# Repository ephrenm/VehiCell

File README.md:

**Goal:** Create a single module which combines vehicle CANbus, GPS and accelerometer data into a single stream to be stored in a cloud database using LTE CAT-M1 cellular technology.

**Current Task:** Routing

Current WIP layout:

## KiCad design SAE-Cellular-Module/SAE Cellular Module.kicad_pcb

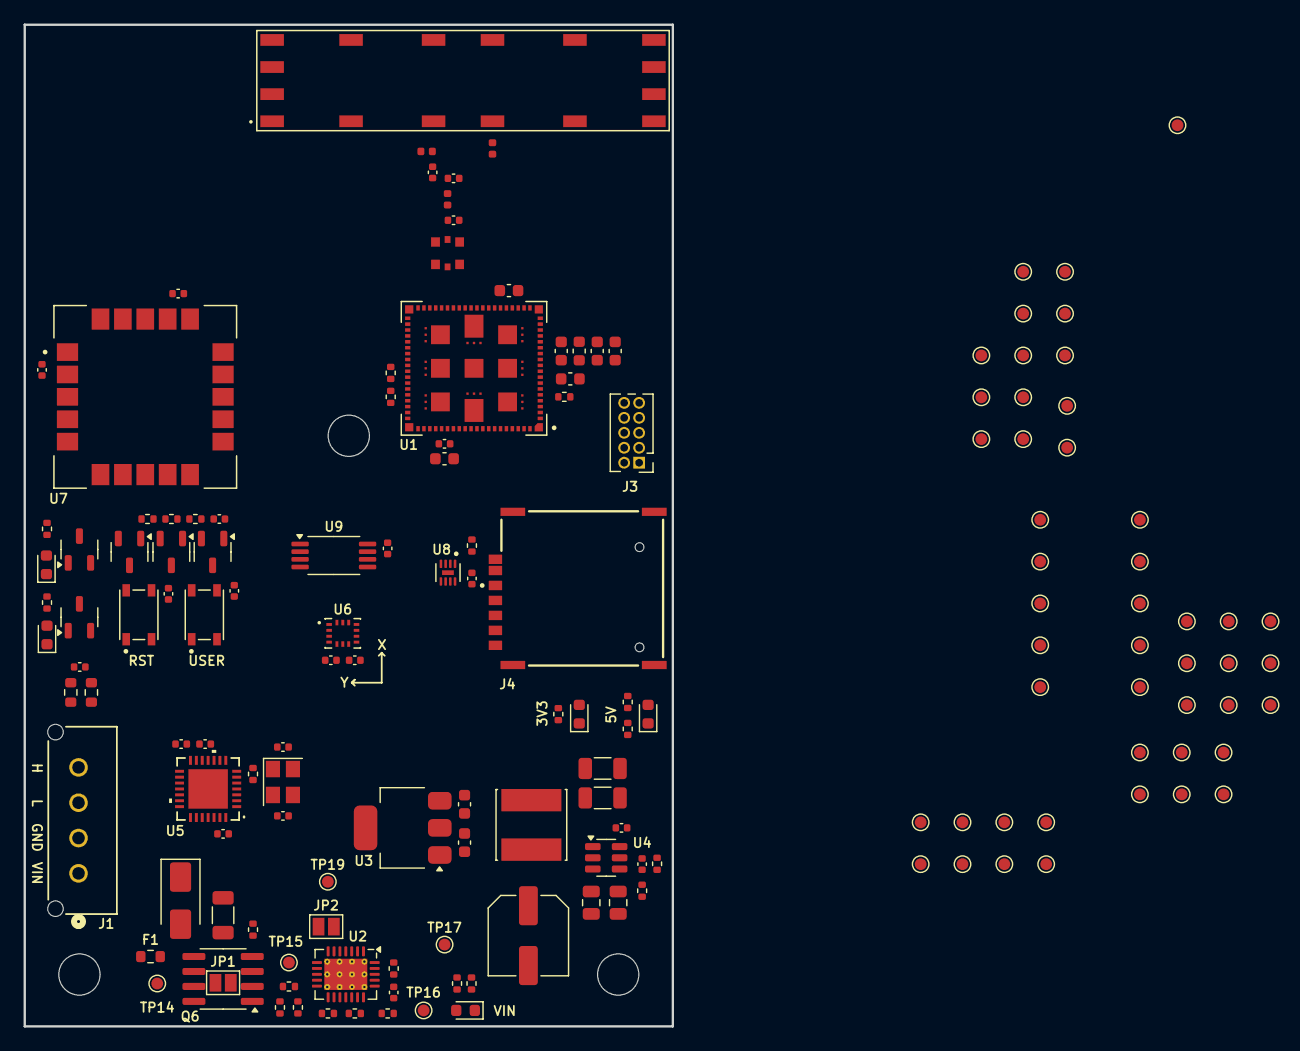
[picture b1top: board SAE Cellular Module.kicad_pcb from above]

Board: 4 copper layers, 55.0 x 85.0 mm, 152 parts (0 on the bottom side), 92 nets, no tracks yet.

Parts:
ANT1: SR4L002; XCVR_SR4L002
C1, C2, C22: 1u; C_0603_1608Metric
C3, C4: 10u; C_0603_1608Metric
C5, C7, C23: 4.7u; C_0603_1608Metric
C6, C11, C12, C13, C15, C16, C26, C29, C30, C31, C32, C33, C34, C35, C36, C37: 100n; C_0402_1005Metric
C8: 2.2p; C_0402_1005Metric
C9: 0.5p; C_0402_1005Metric
C10: C_0402_1005Metric
C14: 1u; C_1206_3216Metric
C18: 47u; C_Elec_6.3x5.4
C19, C20: 10u; C_0805_2012Metric
C21: 75p; C_0402_1005Metric
C24, C25: 22u; C_1206_3216Metric
C28, C38: 36p; C_0402_1005Metric
D1, D2: ORNG; LED_0603_1608Metric
D3: 36V; D_SMA
D4, D5, D6: GRN; LED_0603_1608Metric
F1: 3A; R_0603_1608Metric
FB1: 22R@100M; L_0603_1608Metric
J1: Microfit 3.0; CONN_SD-43650-010_04_MOL
J2: MM8130-2600; MURATA_MM8130-2600RA2
J3: SWD; PinHeader_2x05_P1.27mm_Vertical
J4: SIM8066-6-1-14-01-A; GCT_SIM8066-6-1-14-01-A_REVA
JP1: Jumper_2_Bridged; SolderJumper-2_P1.3mm_Open_Pad1.0x1.5mm
JP2: Jumper_2_Open; SolderJumper-2_P1.3mm_Open_Pad1.0x1.5mm
L1: 3.3n; L_0402_1005Metric
L2, L3: 15n; L_0402_1005Metric
L4: 15u; IND_VLS6045EX-150M
Q1: DMP2004K; SOT-23-3
Q2, Q3, Q4, Q5: DMN2005K; SOT-23-3
Q6: PMOS; SOIC-8_3.9x4.9mm_P1.27mm
R1, R2, R9, R16, R18, R19, R20: 13.3k; R_0402_1005Metric
R3, R17: 100k; R_0402_1005Metric
R4, R7, R8, R21, R22, R23, R27: 330; R_0402_1005Metric
R5, R6: 1M; R_0402_1005Metric
R10: 634k; R_0402_1005Metric
R11, R14: 54.9k; R_0402_1005Metric
R12, R13: 30.1k; R_0402_1005Metric
R15: 5.36k; R_0402_1005Metric
R24, R25: 60R4; R_0603_1608Metric
R26: 0R; R_0402_1005Metric
SW1, SW2: PTS810_SJM_250_SMTR_LFS; SW_PTS810_SJM_250_SMTR_LFS
TP1, TP2, TP3, TP4, TP5, TP6, TP7, TP8, TP9, TP10, TP11, TP12, TP13, TP14, TP15, TP16, TP17, TP18, TP19, TP20, TP21, TP22, TP23, TP24, TP25, TP26, TP27, TP28, TP29, TP30, TP31, TP32, TP33, TP34, TP35, TP36, TP37, TP38, TP39, TP40, TP41, TP42, TP43, TP44, TP45, TP46, TP47, TP48, TP49, TP50, TP51, TP52: TestPoint; TestPoint_Pad_D1.0mm
U1: NRF9151-LACA-R; XCVR_NRF9151-LACA-R
U2: TPS26600RHF; Texas_RHF0024A_VQFN-24-1EP_4x5mm_P0.5mm_EP2.65x3.65mm_Therm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
U3: LDL1117S33R; SOT-223-3_TabPin2
U4: TPS54202DDC; SOT-23-6
U5: MCP251863T-E-9PX; VQFN28_9PX_3p25X3p25EPAD_MCH
U6: BMI270; XDCR_BMI270
U7: SAM-M10Q-00B; XCVR_SAM-M10Q-00B
U8: EMIF03-SIM02M8; SON40P170X150X60-9N
U9: 23K256T-I/ST; TSSOP-8_4.4x3mm_P0.65mm
Y2: 20MHz; Crystal_SMD_Abracon_ABM8G-4Pin_3.2x2.5mm

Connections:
+3V3: C1.1, C2.1, C3.1, C5.1, C6.1, C23.1, C29.1, C30.1, C32.1, C33.1, C34.1, C35.1, C37.1, FB1.1, J3.1, R2.1, R7.1, R8.1, R23.1, TP19.1, U1.65 (VDD_GPIO), U3.2 (VOUT), U5.14 (VIO), U5.26 (VDD), U6.5 (VDDIO), U6.8 (VDD), U7.2 (V_IO), U7.17 (VCC), U9.8 (VCC)
+5V: C21.1, C22.1, C24.1, C25.1, C31.1, L4.2, R17.2, R21.1, TP18.1, U3.3 (VIN), U5.13 (VCC)
/Accelerometer/IMU_CS: TP32.1, U6.12 (CSB)
/Accelerometer/IMU_INT1: TP33.1, U6.4 (INT1)
/Accelerometer/IMU_INT2: TP34.1, U6.9 (INT2)
/Accelerometer/IMU_MISO: TP29.1, U6.1 (SDO)
/Accelerometer/IMU_MOSI: TP30.1, U6.14 (SDX)
/Accelerometer/IMU_SCK: TP31.1, U6.13 (SCX)
/CAN_N: J1.3, R25.2, U5.16 (CANL)
/CAN_P: J1.4, R24.1, U5.17 (CANH)
/CANbus/CAN1_MISO: TP22.1, U5.24 (SDO)
/CANbus/CAN1_MOSI: TP25.1, U5.23 (SDI)
/CANbus/CAN1_SCK: TP23.1, U5.22 (SCK)
/CANbus/CAN1_STBY: TP21.1, U5.18 (STBY)
/CANbus/CAN1_~CS: TP26.1, U5.25 (~CS)
/CANbus/CAN1_~INT0: TP24.1, U5.9 (~INT0)
/CANbus/CAN1_~INT1: TP28.1, U5.8 (~INT1)
/CANbus/CAN1_~INT: TP27.1, U5.3 (~INT)
/NRF9151/COEX0: R5.1, TP12.1, U1.52 (COEX0)
/NRF9151/EXT_RST: C11.1, J3.10, Q1.2 (G), Q3.2 (G), R3.1, SW1.3, SW1.4
/NRF9151/GPS_EXTINT: TP40.1, U7.19 (EXTINT)
/NRF9151/GPS_RXD: TP42.1, U7.14 (RXD)
/NRF9151/GPS_TXD: TP41.1, U7.13 (TXD)
/NRF9151/GPS_~RESET: TP36.1, U7.18 (~RESET)
/NRF9151/SIM_CD: R27.2, U1.26 (SIM_DET)
/NRF9151/SWDCLK: J3.4, TP4.1, U1.3 (SWDCLK)
/NRF9151/SWDIO: J3.2, TP5.1, U1.4 (SWDIO)
/NRF9151/USER_SW: C12.1, SW2.3, SW2.4
/NRF9151/~RESET: C13.1, R4.2, TP3.1, U1.9 (~RESET)
/Power/VIN: F1.1, J1.1
/SIM Card/SIM_1V8: C36.1, J4.C1 (VCC), TP43.1, U1.19 (SIM_1V8), U8.1 (VCC), U8.8 (VCC)
/SIM Card/SIM_CLK: J4.C3 (CLK), TP45.1, U1.18 (SIM_CLK), U8.3 (CLKIN), U8.6 (CLKEXT)
/SIM Card/SIM_DET: J4.CD, R27.1, TP47.1
/SIM Card/SIM_IO: J4.C7 (I/O), TP46.1, U1.17 (SIM_IO), U8.4 (DATAIN), U8.5 (DATAEXT)
/SIM Card/SIM_RST: J4.C2 (RST), TP44.1, U1.16 (SIM_RST), U8.2 (RSTIN), U8.7 (RSTEXT)
/SRAM/SRAM_MISO: TP49.1, U9.2 (SO)
/SRAM/SRAM_MOSI: TP48.1, U9.5 (SI)
/SRAM/SRAM_SCK: TP50.1, U9.6 (SCK)
/SRAM/SRAM_~CS: TP51.1, U9.1 (~CS)
/SRAM/SRAM_~HOLD: TP52.1, U9.7 (~HOLD)
GND: C1.2, C2.2, C3.2, C4.2, C5.2, C6.2, C7.2, C9.1, C10.1, C11.2, C12.2, C13.2, C14.2, C18.2, C19.2, C20.2, C22.2, C23.2, C24.2, C25.2, C26.2, C28.1, C29.2, C30.2, C31.2, C32.2, C33.2, C34.2, C35.2, C36.2, C37.2, C38.1, D3.1 (A1), D4.1 (K), D5.1 (K), D6.1 (K), J1.2, J2.GND1 (GND), J2.GND2 (GND), J2.GND3 (GND), J2.GND4 (GND), J3.3, J3.5, J3.9, J4.C5 (GND), J4.G1 (GND__1), J4.G2 (GND__2), J4.G3 (GND__3), J4.G4 (GND__4), L2.1, L3.1, Q2.3 (S), Q3.3 (S), Q4.3 (S), Q5.3 (S), R5.2, R6.2, R9.2, R18.2, SW1.1, SW1.2, SW2.1, SW2.2, U1.1 (GND_1), U1.7 (GND_1__1), U1.13 (GND_1__2), U1.15 (GND_1__3), U1.20 (GND_1__4), U1.25 (GND_1__5), U1.30 (GND_1__6), U1.34 (GND_1__7), U1.36 (GND_1__8), U1.38 (GND_1__9), U1.39 (GND_1__10), U1.40 (GND_1__11), U1.41 (GND_1__12), U1.43 (GND_1__13), U1.46 (GND_1__14), U1.51 (GND_2), U1.55 (GND_2__1), U1.60 (GND_2__2), U1.66 (GND_2__3), U1.71 (GND_2__4), U1.76 (GND_2__5), U1.105 (GND_2__6), U1.106 (GND_2__7), U1.107 (GND_2__8), U1.108 (GND_2__9), U1.109 (GND_2__10), U1.110 (GND_2__11), U1.111 (GND_2__12), U1.112 (GND_2__13), U1.113 (GND_2__14), U2.17 (GND), U3.1 (GND), U4.1 (GND), U5.7 (VSS), U5.10 (GND), U6.6 (GNDIO), U6.7 (GND), U7.1 (GND), U7.4 (GND__1), U7.5 (GND__2), U7.6 (GND__3), U7.10 (GND__4), U7.11 (GND__5), U7.15 (GND__6), U7.16 (GND__7), U7.20 (GND__8), U8.9 (GND), U9.4 (VSS), Y2.2, Y2.4
unnamed: ANT1.3 (FEED), C8.2, L2.2
unnamed: ANT1.4 (RETURN/GND), L3.2
unnamed: C9.2, J2.IN, L1.1
unnamed: C8.1, C10.2, L1.2
unnamed: C26.1, R24.2, R25.1
unnamed: C28.2, R26.1, Y2.1
unnamed: D1.2 (A), R7.2
unnamed: D1.1 (K), Q4.1 (D)
unnamed: D2.2 (A), R8.2
unnamed: D2.1 (K), Q5.1 (D)
unnamed: C14.1, D3.2 (A2), F1.2, JP1.1 (A), Q6.5 (D), Q6.6 (D), Q6.7 (D), Q6.8 (D), TP14.1
unnamed: D4.2 (A), R19.2, R20.2
unnamed: D5.2 (A), R22.2
unnamed: D6.2 (A), R23.2
unnamed: JP1.2 (B), JP2.1 (A), Q6.1 (S), Q6.2 (S), Q6.3 (S), R10.1, TP15.1, U2.8 (IN), U2.9 (IN)
unnamed: Q1.1 (D), R2.2, R3.2
unnamed: Q1.3 (S), Q2.2 (G), Q3.1 (D)
unnamed: Q2.1 (D), R4.1
unnamed: Q6.4 (G), R9.1
unnamed: R21.2, R22.1
unnamed: J2.OUT, U1.35 (ANT)
unnamed: C7.1, U1.24 (DEC0)
unnamed: R1.2, TP2.1, U1.10 (ENABLE)
unnamed: C4.1, FB1.2, R1.1, TP1.1, U1.14 (VDD)
unnamed: R6.1, TP13.1, U1.54 (COEX2)
unnamed: TP6.1, U1.21 (MAGPIO0)
unnamed: TP7.1, U1.22 (MAGPIO1)
unnamed: TP8.1, U1.23 (MAGPIO2)
unnamed: TP10.1, U1.28 (SCLK)
unnamed: TP9.1, U1.27 (SDATA)
unnamed: TP11.1, U1.29 (VIO)
unnamed: R15.1, U2.19 (ILIM)
unnamed: R14.1, R16.1, U2.18 (IMON)
unnamed: C15.2, R12.2, R15.2, R16.2, U2.13 (MODE), U2.14 (~SHDN), U2.15 (RTN), U2.25 (RTN)
unnamed: R11.2, R12.1, U2.12 (OVP)
unnamed: R10.2, R11.1, U2.10 (UVLO)
unnamed: C15.1, U2.20 (dVdT)
unnamed: R13.2, TP16.1, U2.22 (~FLT)
unnamed: C16.1, U4.6 (BOOT)
unnamed: C21.2, R17.1, R18.1, U4.4 (FB)
unnamed: C16.2, L4.1, U4.2 (SW)
unnamed: TP20.1, U5.2 (CLKO)
unnamed: R26.2, U5.5 (OSC1)
unnamed: C38.2, U5.4 (OSC2), Y2.3
unnamed: U5.1 (RXCAN), U5.11 (RXD)
unnamed: U5.20 (TXD), U5.28 (TXCAN)
unnamed: TP39.1, U7.12 (SCL)
unnamed: TP37.1, U7.9 (SDA)
unnamed: TP35.1, U7.7 (TIMEPULSE)
unnamed: TP38.1, U7.8 (~SAFEBOOT)
VOUT: C18.1, C19.1, C20.1, JP2.2 (B), R13.1, R19.1, R20.1, TP17.1, U2.23 (OUT), U2.24 (OUT), U4.3 (VIN)

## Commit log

2025-06-11 Initial Push
2025-06-11 Create SAE-Cellular-Module
2025-06-11 Initial
2025-07-03 Added initial component placements
